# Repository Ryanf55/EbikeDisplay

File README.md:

This repo is for an Ebike Controller. It contains a PCB for Nokia 5110 LCD, SolidWorks files / STL's for the case, and Arduino code to work with a cyclone. 

Cyclone throttle cable pinout:
* blue - Vbat 
* black - gnd
* yellow- ignition (connect to Vbat to turn system on)
* green - throttle 0 to 3.3v

stock hall: D49E 503D

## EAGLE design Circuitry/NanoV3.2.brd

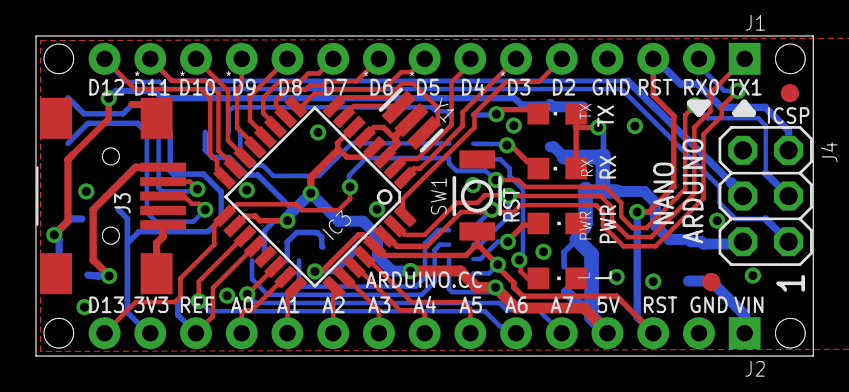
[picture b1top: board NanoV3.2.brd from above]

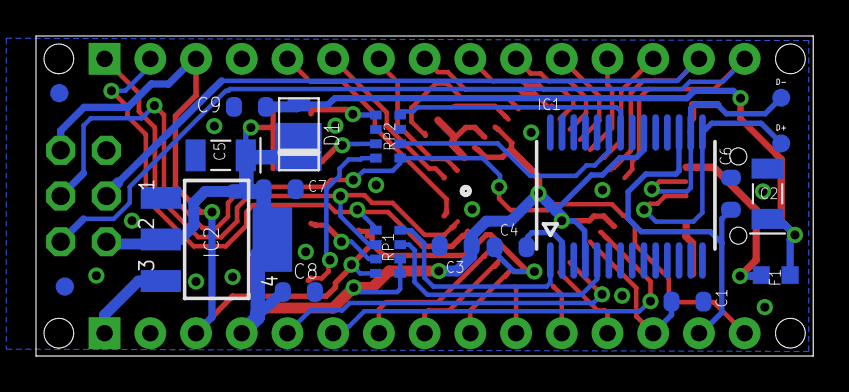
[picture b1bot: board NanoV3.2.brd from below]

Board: 2 copper layers, 43.2 x 17.8 mm, 33 parts (17 on the bottom side), 43 nets.

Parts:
C1, C4, C6, C9: 100nF; C0603-ROUND
C2, C5: 4,7uF_16V; TAN-A
C3, C7, C8: 1uF; C0603-ROUND
D1: SS1P3L; DO220AAL
D+: DNP; TP-1.00MM
D-: DNP; TP-1.00MM
F1: MFFSMF050; 0603-1608X90N
FRAME1: DNP; FRAME
IC1: FT232RL; SSOP28
IC2: LM1117IMPX-5.0; LINEAR_SOT223
IC3: ATMEGA328P-AU; TQFP32-08
J1, J2: XXXX_STRIPNANO; HEAD15-NOSS
J3: USB-MINI-B_2
J4: 2X03
L: Yellow; CHIPLED_0805
PWR: Green; CHIPLED_0805
RP1, RP2: 1K; CAY16
RX: Red; CHIPLED_0805
SW1: RESET; SMD_157SW
TX: Green; CHIPLED_0805
U$4, U$5, U$53, U$54: DNP; FD-1-1.5
Y1: 16MHz; RESONATOR

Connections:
3V3: C6.2, IC1.17, J2.14
+5V: C3.1, C5.1, C7.1, C8.1, D1.P$1, IC1.4, IC1.20, IC2.2, IC2.4, IC3.4, IC3.6, IC3.18, J2.4, J4.2, RP1.5, RP1.6, RX.A, TX.A
A0: IC3.23, J2.12
A1: IC3.24, J2.11
A2: IC3.25, J2.10
A3: IC3.26, J2.9
A4: IC3.27, J2.8
A5: IC3.28, J2.7
A6: IC3.19, J2.6
A7: IC3.22, J2.5
AREF: C1.1, IC3.20, J2.13
COM: C1.2, C2.2, C3.2, C5.2, C6.1, C7.2, C8.2, C9.2, IC1.7, IC1.18, IC1.21, IC1.25, IC1.26, IC2.1, IC3.3, IC3.5, IC3.21, J1.4, J2.2, J3.1, J3.6, J3.7, J3.8, J3.9, J4.6, L.C, PWR.C, RP2.3, RP2.6, SW1.1, Y1.2
D0/RX: IC3.30, J1.2, RP1.1
D1/TX: IC3.31, J1.1, RP1.2
D2: IC3.32, J1.5
D3: IC3.1, J1.6
D4: IC3.2, J1.7
D5: IC3.9, J1.8
D6: IC3.10, J1.9
D7: IC3.11, J1.10
D8: IC3.12, J1.11
D9: IC3.13, J1.12
D10: IC3.14, J1.13
D11/MOSI: IC3.15, J1.14, J4.4
D12/MISO: IC3.16, J1.15, J4.1
D13/SCK: IC3.17, J2.15, J4.3, RP2.1
unnamed: IC3.8, Y1.3
unnamed: IC3.7, Y1.1
unnamed: PWR.A, RP1.3
unnamed: C4.2, IC1.2
unnamed: D+.X, IC1.15, J3.3
unnamed: D-.X, IC1.16, J3.4
unnamed: L.A, RP2.8
unnamed: IC1.23, RP2.2
unnamed: IC1.22, RP2.4
unnamed: RP2.5, TX.C
unnamed: F1.2, J3.5
unnamed: RP2.7, RX.C
RESET: C4.1, IC3.29, J1.3, J2.3, J4.5, RP1.4, SW1.2
RX: IC1.1, RP1.8
TX: IC1.5, RP1.7
VIN: IC2.3, J2.1
VUSB: C2.1, C9.1, D1.P$2, F1.1

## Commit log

2019-04-28 Formatting fixes
2019-04-28 Snowy Ebike Image
2019-06-21 add throttle pinout for cyclone
2019-06-21 formatting
2021-04-02 Modify to support correct pins
    * Correct bug in throttle conversion from hall to output
    * Add expo filtering on output throttle signal
    * Add conversion to battery percentage
2021-04-17 Fix calibration value for voltage

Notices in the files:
parts and their libraries:
Arduino-utility: Copyright (c) 2016-2017 Arduino LLC.  All right reserved.
